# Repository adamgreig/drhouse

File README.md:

DrHouse
=======

House related code. Amongst other things.

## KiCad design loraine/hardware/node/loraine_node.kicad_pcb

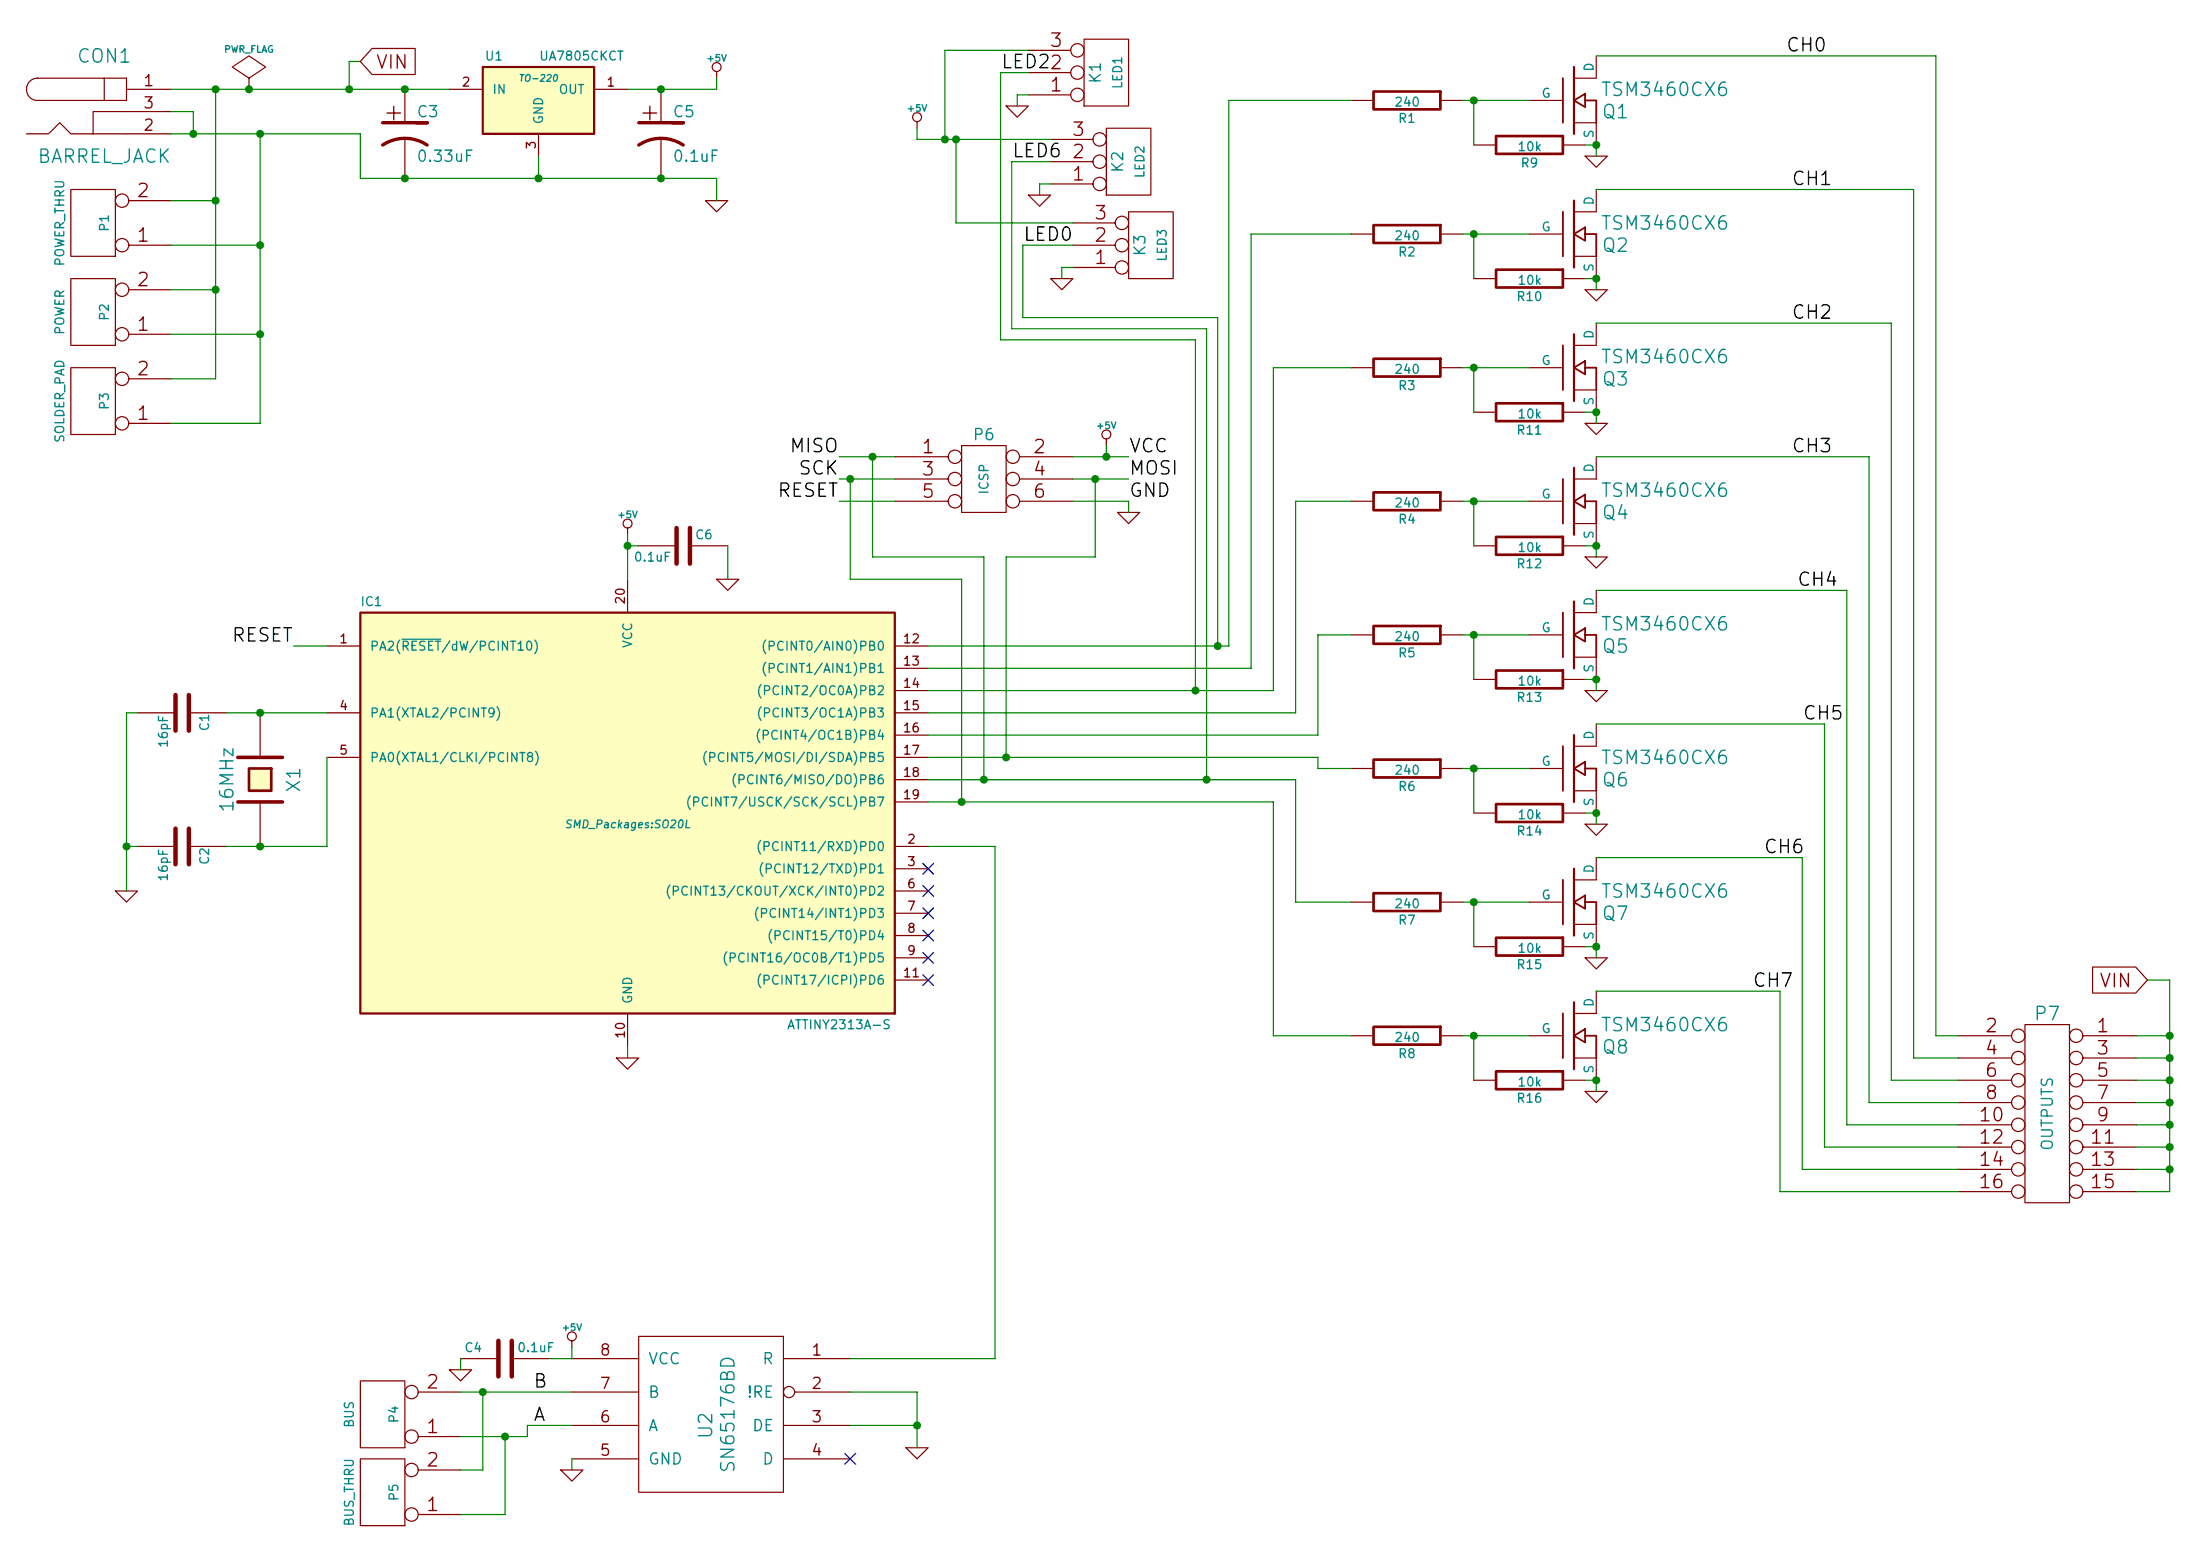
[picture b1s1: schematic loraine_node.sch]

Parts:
C1, C2: 16pF; c_0805
C3: 0.33uF; c_0805
C4, C5, C6: 0.1uF; c_0805
CON1: BARREL_JACK
IC1: ATTINY2313A-S; SO20L
K1: LED1; SIL-3
K2: LED2; SIL-3
K3: LED3; SIL-3
P1: POWER_THRU; SIL-2
P2: POWER; SIL-2
P3: SOLDER_PAD; SIL-2
P4: BUS; Pin_Header_Straight_2x03
P5: BUS_THRU; Pin_Header_Straight_2x08
P6: ICSP; SIL-2
P7: OUTPUTS; SIL-2
Q1, Q2, Q3, Q4, Q5, Q6, Q7, Q8: TSM3460CX6; TO126
R1, R2, R3, R4, R5, R6, R7, R8: 240; SM0805
R9, R10, R11, R12, R13, R14, R15, R16: 10k; SM0805
U1: UA7805CKCT; TO-220
U2: SN65176BD; SO8E
X1: 16MHz; Crystal_HC49-SD_SMD

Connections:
+5V: C4.2, C5.1, C6.2, IC1.20 (VCC), K1.3, K2.3, K3.3, P6.2, U1.1 (OUT), U2.8 (VCC); also elsewhere on the board
/A: P4.1, P5.1, U2.6 (A)
/B: P4.2 (PM), P5.2 (PM), U2.7 (B)
/CH0: P7.2, Q1.D
/CH1: P7.4, Q2.D
/CH2: P7.6, Q3.D
/CH3: P7.8, Q4.D
/CH4: P7.10, Q5.D
/CH5: P7.12, Q6.D
/CH6: P7.14, Q7.D
/CH7: P7.16, Q8.D
/LED0: IC1.12 ((PCINT0/AIN0)PB0), K3.2 (PM), R1.2
/LED2: IC1.14 ((PCINT2/OC0A)PB2), K1.2 (PM), R3.2
/LED6: IC1.18 ((PCINT6/MISO/DO)PB6), K2.2 (PM), P6.1, R7.2
/MOSI: IC1.17 ((PCINT5/MOSI/DI/SDA)PB5), P6.4, R6.2
/RESET: IC1.1 (PA2(~RESET~/dW/PCINT10)), P6.5
/SCK: IC1.19 ((PCINT7/USCK/SCK/SCL)PB7), P6.3, R8.2
GND: C1.2, C2.2, C3.2, C4.1, C5.2, C6.1, CON1.2, CON1.3, IC1.10 (GND), K1.1, K2.1, K3.1, P1.1, P2.1, P3.1, P6.6, Q1.S, Q2.S, Q3.S, Q4.S, Q5.S, Q6.S, Q7.S, Q8.S, R9.1, R10.1, R11.1, R12.1, R13.1, R14.1, R15.1, R16.1, U1.3 (GND), U2.2 (!RE), U2.3 (DE), U2.5 (GND)
unnamed: C1.1, IC1.4 (PA1(XTAL2/PCINT9)), X1.1
unnamed: C2.1, IC1.5 (PA0(XTAL1/CLKI/PCINT8)), X1.2
unnamed 20: IC1.2 ((PCINT11/RXD)PD0), U2.1 (R); also elsewhere on the board
unnamed: IC1.13 ((PCINT1/AIN1)PB1), R2.2
unnamed: IC1.15 ((PCINT3/OC1A)PB3), R4.2
unnamed: IC1.16 ((PCINT4/OC1B)PB4), R5.2
unnamed: Q1.G, R1.1, R9.2
unnamed: Q2.G, R2.1, R10.2
unnamed: Q3.G, R3.1, R11.2
unnamed: Q4.G, R4.1, R12.2
unnamed: Q5.G, R5.1, R13.2
unnamed: Q6.G, R6.1, R14.2
unnamed: Q7.G, R7.1, R15.2
unnamed: Q8.G, R8.1, R16.2
VIN: C3.1, CON1.1, P1.2 (PM), P2.2 (PM), P3.2 (PM), P7.1, P7.3, P7.5, P7.7, P7.9, P7.11, P7.13, P7.15, U1.2 (IN)

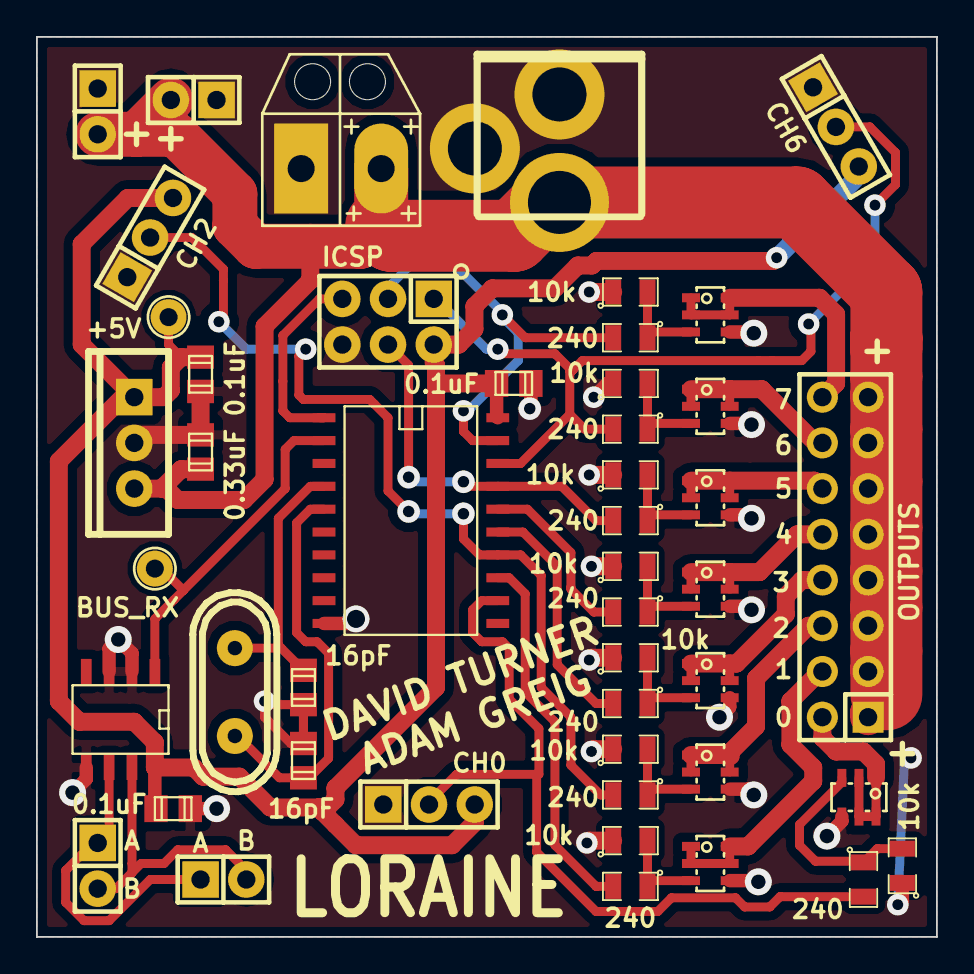
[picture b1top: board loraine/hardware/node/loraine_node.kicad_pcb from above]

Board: 2 copper layers, 50.0 x 50.0 mm, 47 parts (0 on the bottom side), 33 nets.

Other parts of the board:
P8: +5V; TESTPOINT
P9: BUS_RX; TESTPOINT

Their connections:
+5V: P8.1; also elsewhere on the board
unnamed 20: P9.1; also elsewhere on the board

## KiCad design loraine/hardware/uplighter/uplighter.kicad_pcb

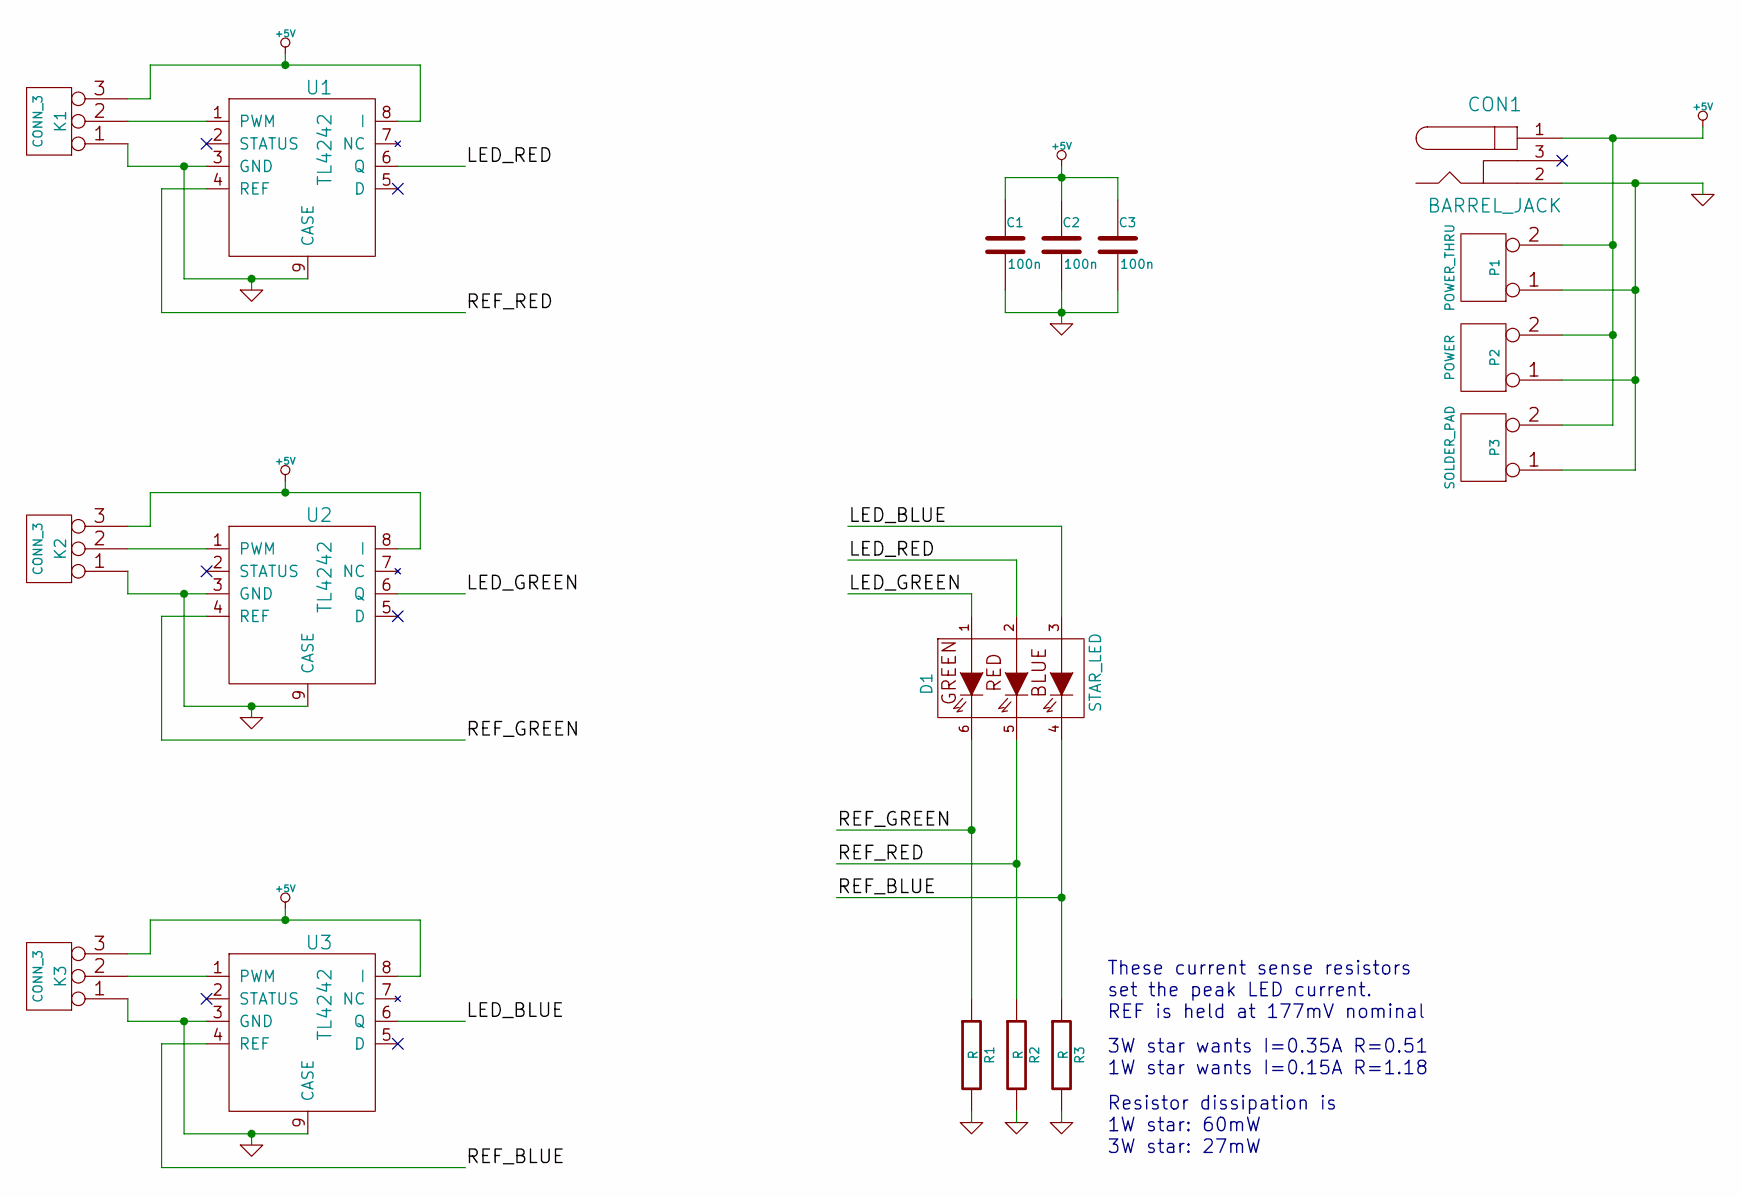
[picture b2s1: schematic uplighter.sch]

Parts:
C1, C2, C3: 100n
CON1: BARREL_JACK
D1: STAR_LED
K1, K2, K3: CONN_3
P1: POWER_THRU
P2: POWER
P3: SOLDER_PAD
R1, R2, R3: R
U1, U2, U3: TL4242

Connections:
+5V: C1.1, C2.1, C3.1, CON1.1, K1.3, K2.3, K3.3, P1.2 (PM), P2.2 (PM), P3.2 (PM), U1.8 (I), U2.8 (I), U3.8 (I)
/LED_BLUE: D1.3 (B+), U3.6 (Q)
/LED_GREEN: D1.1 (G+), U2.6 (Q)
/LED_RED: D1.2 (R+), U1.6 (Q)
/REF_BLUE: D1.4 (B-), R3.1, U3.4 (REF)
/REF_GREEN: D1.6 (G-), R1.1, U2.4 (REF)
/REF_RED: D1.5 (R-), R2.1, U1.4 (REF)
GND: C1.2, C2.2, C3.2, CON1.2, CON1.3, K1.1, K2.1, K3.1, P1.1, P2.1, P3.1, R1.2, R2.2, R3.2, U1.3 (GND), U1.9 (CASE), U2.3 (GND), U2.9 (CASE), U3.3 (GND), U3.9 (CASE)
unnamed: K1.2 (PM), U1.1 (PWM)
unnamed: K2.2 (PM), U2.1 (PWM)
unnamed: K3.2 (PM), U3.1 (PWM)

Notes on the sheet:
These current sense resistors set the peak LED current. REF is held at 177mV nominal
3W star wants I=0.35A R=0.51 1W star wants I=0.15A R=1.18
Resistor dissipation is 1W star: 60mW 3W star: 27mW

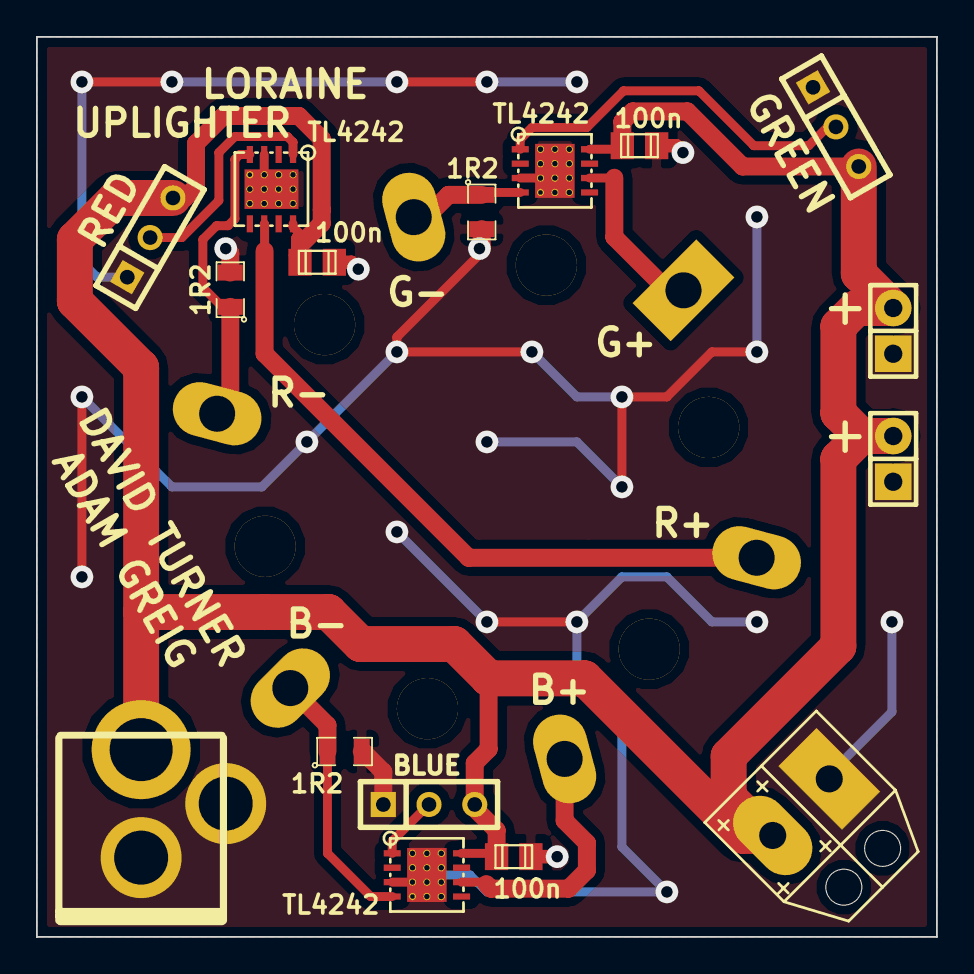
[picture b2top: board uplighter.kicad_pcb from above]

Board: 2 copper layers, 50.0 x 50.0 mm, 17 parts (0 on the bottom side), 11 nets.

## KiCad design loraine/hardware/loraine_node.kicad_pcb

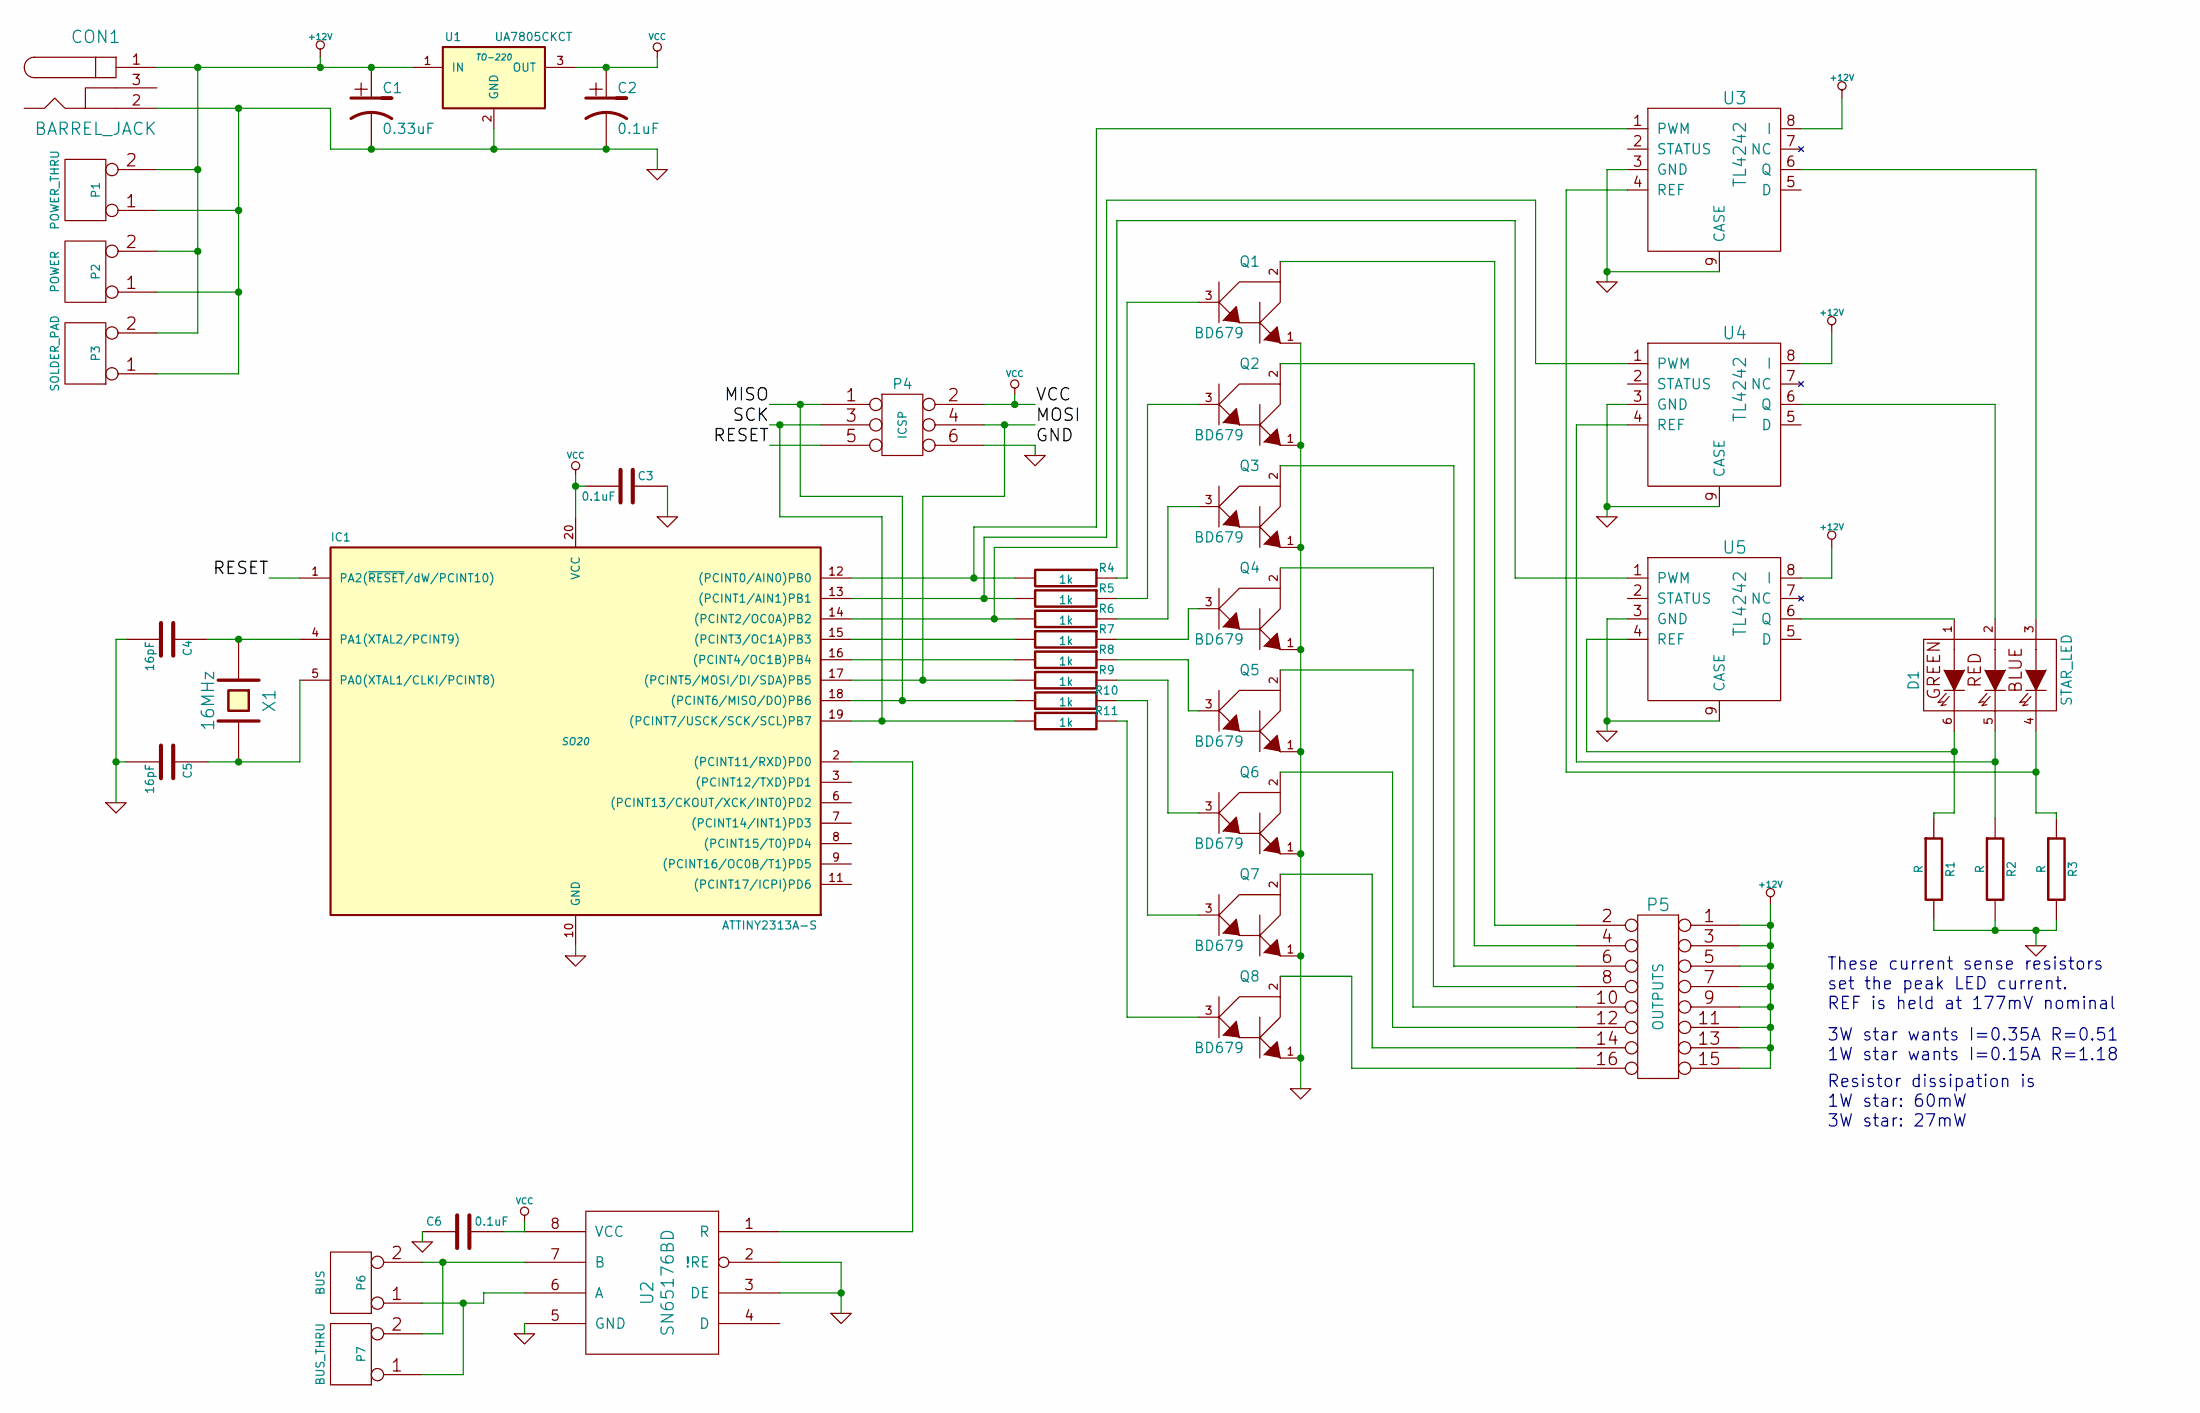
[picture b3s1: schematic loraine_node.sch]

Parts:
C1: 0.33uF
C2, C3, C6: 0.1uF
C4, C5: 16pF
CON1: BARREL_JACK
D1: STAR_LED
IC1: ATTINY2313A-S; SO20
P1: POWER_THRU
P2: POWER
P3: SOLDER_PAD
P4: ICSP
P5: OUTPUTS
P6: BUS
P7: BUS_THRU
Q1, Q2, Q3, Q4, Q5, Q6, Q7, Q8: BD679
R1, R2, R3: R
R4, R5, R6, R7, R8, R9, R10, R11: 1k
U1: UA7805CKCT; TO-220
U2: SN65176BD
U3, U4, U5: TL4242
X1: 16MHz

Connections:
+12V: C1.1, CON1.1, P1.2 (PM), P2.2 (PM), P3.2 (PM), P5.1, P5.3, P5.5, P5.7, P5.9, P5.11, P5.13, P5.15, U1.1 (IN), U3.8 (I), U4.8 (I), U5.8 (I)
/MISO: IC1.18 ((PCINT6/MISO/DO)PB6), P4.1, R10.2
/MOSI: IC1.17 ((PCINT5/MOSI/DI/SDA)PB5), P4.4, R9.2
/RESET: IC1.1 (PA2(~RESET~/dW/PCINT10)), P4.5
/SCK: IC1.19 ((PCINT7/USCK/SCK/SCL)PB7), P4.3, R11.2
GND: C1.2, C2.2, C3.1, C4.2, C5.2, C6.1, CON1.2, IC1.10 (GND), P1.1, P2.1, P3.1, P4.6, Q1.1, Q2.1, Q3.1, Q4.1, Q5.1, Q6.1, Q7.1, Q8.1, R1.2, R2.2, R3.2, U1.2 (GND), U2.2 (!RE), U2.3 (DE), U2.5 (GND), U3.3 (GND), U3.9 (CASE), U4.3 (GND), U4.9 (CASE), U5.3 (GND), U5.9 (CASE)
unnamed: C4.1, IC1.4 (PA1(XTAL2/PCINT9)), X1.1
unnamed: C5.1, IC1.5 (PA0(XTAL1/CLKI/PCINT8)), X1.2
unnamed: D1.1 (G+), U5.6 (Q)
unnamed: D1.2 (R+), U4.6 (Q)
unnamed: D1.3 (B+), U3.6 (Q)
unnamed: D1.4 (B-), R3.1, U3.4 (REF)
unnamed: D1.5 (R-), R2.1, U4.4 (REF)
unnamed: D1.6 (G-), R1.1, U5.4 (REF)
unnamed: IC1.2 ((PCINT11/RXD)PD0), U2.1 (R)
unnamed: IC1.12 ((PCINT0/AIN0)PB0), R4.2, U3.1 (PWM)
unnamed: IC1.13 ((PCINT1/AIN1)PB1), R5.2, U4.1 (PWM)
unnamed: IC1.14 ((PCINT2/OC0A)PB2), R6.2, U5.1 (PWM)
unnamed: IC1.15 ((PCINT3/OC1A)PB3), R7.2
unnamed: IC1.16 ((PCINT4/OC1B)PB4), R8.2
unnamed: P5.2, Q1.2
unnamed: P5.4, Q2.2
unnamed: P5.6, Q3.2
unnamed: P5.8, Q4.2
unnamed: P5.10, Q5.2
unnamed: P5.12, Q6.2
unnamed: P5.14, Q7.2
unnamed: P5.16, Q8.2
unnamed: P6.1, P7.1, U2.6 (A)
unnamed: P6.2 (PM), P7.2 (PM), U2.7 (B)
unnamed: Q1.3, R4.1
unnamed: Q2.3, R5.1
unnamed: Q3.3, R6.1
unnamed: Q4.3, R7.1
unnamed: Q5.3, R8.1
unnamed: Q6.3, R9.1
unnamed: Q7.3, R10.1
unnamed: Q8.3, R11.1
VCC: C2.1, C3.2, C6.2, IC1.20 (VCC), P4.2, U1.3 (OUT), U2.8 (VCC)

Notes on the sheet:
These current sense resistors set the peak LED current. REF is held at 177mV nominal
3W star wants I=0.35A R=0.51 1W star wants I=0.15A R=1.18
Resistor dissipation is 1W star: 60mW 3W star: 27mW

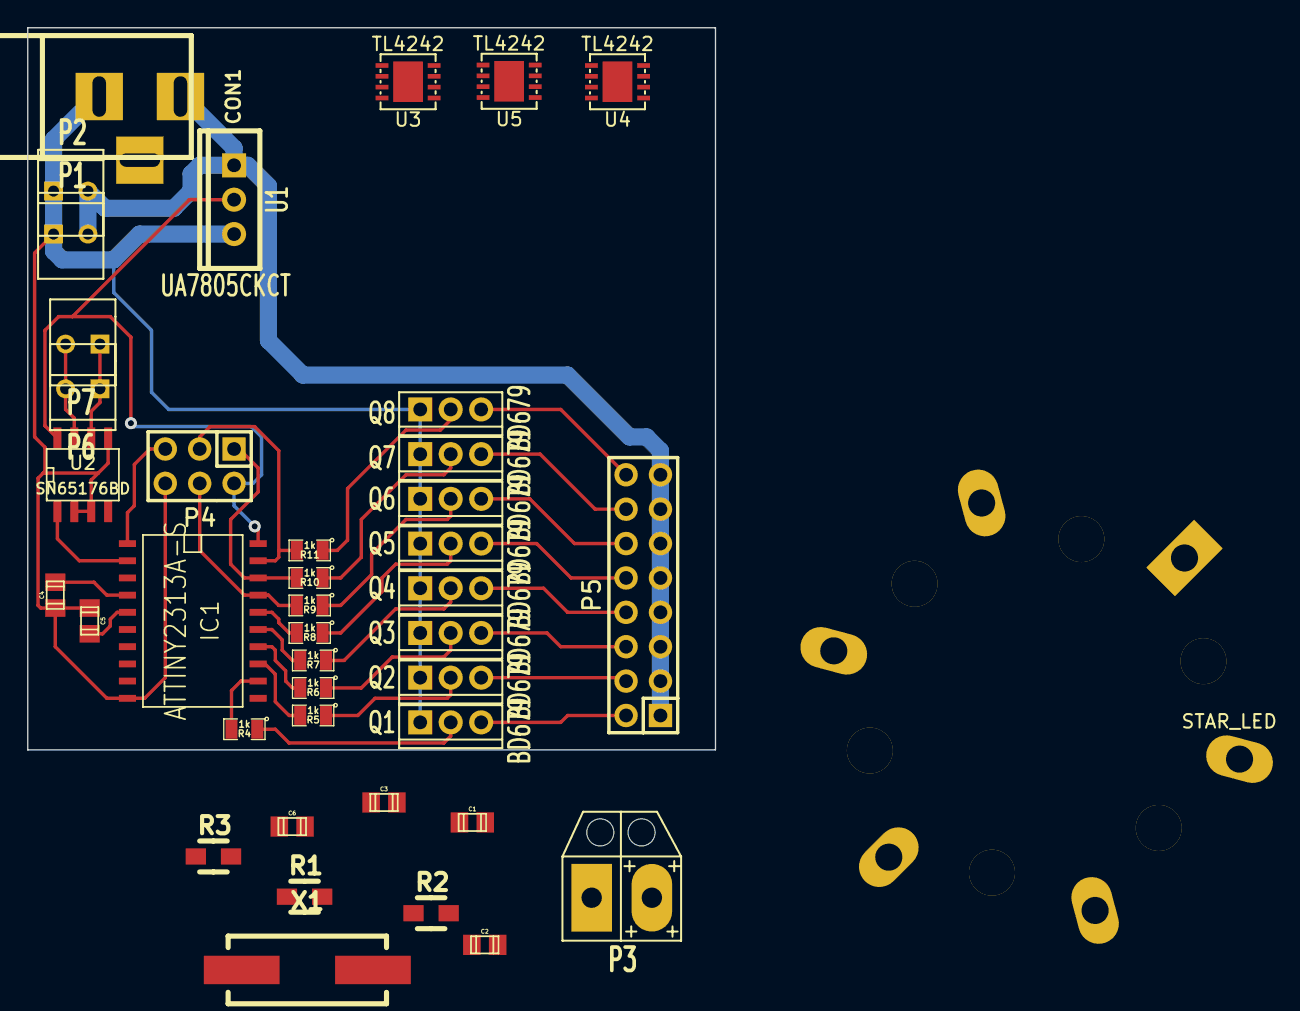
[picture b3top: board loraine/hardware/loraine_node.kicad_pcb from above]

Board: 2 copper layers, 50.8 x 53.3 mm, 41 parts (0 on the bottom side), 39 nets.

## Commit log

2013-12-21 add basic lightstrip control
2013-12-21 fix api bit
2013-12-22 actually use 0-255 on the api
2013-12-22 balance for white point
2013-12-22 colour calibrate against projector
2013-12-23 add android.
2013-12-23 add atmolight
2013-12-23 add beats work
2014-01-25 add first loraine code
2014-01-26 v1 driver and node firmware
2014-01-26 use proper bit names in driver code
2014-01-26 get rid of old prototype driver code
2014-01-27 commit server code
2014-01-28 add broadcast addresses
2014-01-28 add example clients
2014-01-28 Wondering if I can push to this repo.
2014-01-28 Made the vu meter yellow a bit yellower
2014-01-28 Doubled VU speed, made bottom level not always on
2014-01-28 Changed VU speed more for convincing effect
2014-01-28 Initial commit of bookshelf_colour_fade.py
2014-01-28 Slowed frequency of direction changes
2014-01-28 Significant refactor and bugfix
2014-01-28 extend test client to whole bookshelf
2014-01-28 add broadcast test scripts
2014-01-28 Added long shift register to colourfade
2014-01-29 Added stdout flush
2014-01-29 Fixed some code style issues
2014-01-29 Made pep8 happy on bookshelf_colur_fade
2014-01-29 Fixed over-long line in bookshelf_vu
2014-01-29 Doubled frequency of random changes
2014-02-09 Added patternator, example pattern function
2014-02-09 updated comments
2014-02-09 Added random_hue patternator
2014-02-09 Add random_hue_walk patternator
2014-02-09 Fixed style err in example_pattern
2014-02-10 temp to rgb transform
2014-02-10 Simplified incandescent simulator
2014-02-10 Changed colours slightly in test_inc
2014-02-11 inctest2 with hand tuned incandescent fade vals
2014-02-11 add cserver
2014-02-11 fit functions based on hand tuned inc sim
2014-02-11 unsigned chars for server.c
2014-02-11 add first go at loraine python lib
2014-02-11 Removed debug message from libloraine
2014-02-11 Updated loraine clients to cserver
2014-02-12 Changed inctest2 to interpolation method
2014-02-12 add comment to driver sketch
2014-02-12 Changed test_incandescent to interp method
2014-02-12 Added basic patternator wrapper
2014-02-12 add first go at VU
2014-02-19 Disabled debug output in bookshelf_colour_fade
2014-02-20 Added patternator incandescent flash
2014-02-24 TODO with fun randombow plans
2014-03-03 Added new incandescent_set script
2014-03-30 Uplighter node hardware schematic
2014-03-30 KiCAD .gitignore file
2014-03-30 Added extra power connectors
2014-03-30 Added ICSP header
2014-03-30 Added common anodes to outputs connector
2014-03-30 Filled in most component values
2014-03-30 Replaced VCC/GND labels with symbols
2014-03-31 Specced darlington drivers
2014-03-31 fairylights!
2014-03-31 py2 compat
2014-03-31 add auto lights
2014-03-31 Initial netlist and most parts
2014-03-31 basic pcb component spread
2014-03-31 Added kicad_pcb-bak to .gitignore
2014-03-31 First attempt at PCB, minus some caps and LEDs
2014-03-31 Changed darlingtons to PTH part
2014-03-31 Added bus thu connector
2014-03-31 PCB rev2
    Routed PTH darlingtons
    swapped order of output pinout to make pcb route better
    'L'-shaped PCB for adam ;)
2014-03-31 Added TL4242 driver ICs with support circuitry
2014-03-31 Moved driver PWM conns to before BJT base resistors.
2014-04-30 Fixed driver current sense lines
    TL4242 current sense lines went to ground instead of top of current sense resistors.
2014-04-30 Added star_led schematic component
    Made new library star_led.lib with schematic component for RGB star LED with pinout matching Farnell 1716741. Footprint to follow.
2014-05-01 Annotated schematic, annotated netlist
2014-05-01 Added TL4242 footprint
2014-05-01 Added star led module footprint
2014-05-01 Added outline to 8-SON footprint
2014-05-01 Added remaining footprints to netlist/pcb
2014-05-01 Added locking 2-way MOLEX headers
    MOLEX part 22-23-2021 for header = farnell 1462926
    MOLEX part 22-01-3027 for receptacle = farnell 1462825
2014-05-01 Added proper solder pad footprint
2014-05-01 Improved power solder pad
    Added strain relief, made pin 1 (negative) rectangular
2014-05-04 Updated BOM
2014-05-09 renamed dir
2014-05-09 Changed LED component/footprint to single colour devices
2014-05-10 Split project into node and uplighter
    Node now contains ATTINY, bus controller and most logic and programing
    Uplighter board is just three LEDs and their drivers (and sense resistors)
    Connection between the two is currently a SIL9 but might be better split into three (or so) connectors so the connectors can stably mount the uplighter board.
2014-05-10 Split board-board connector to 3x SIL3
2014-05-11 Removed separate uplighter board
2014-05-12 Proposed design: 1 board 3x3 RGB LEDs
2014-05-12 Fixed sense resistors in schematic
2014-05-18 Heatsunk LED footprint and board pads
2014-05-18 Square board edge
2014-05-18 Split boards
    Removed LEDs and TL4242s and sense resistors from main node board and added 3x SIL3 connectors
    Added 2nd board containing heatsunk LED mounting, TL4242, sense resistors.
2014-05-19 Added backside copper and thermal vias to 8-son
2014-07-17 Proposed output driver for node h/w
2014-07-20 NMOS drivers on schematic + ERC fixes
2014-07-20 Node PCB redo
2014-07-20 Finished footprint placement on node board
2014-07-20 Cleared up node pcb silk
2014-07-20 Finished both PCBs apart from logos and checking
2014-07-21 5V power conn on uplighter board
2014-07-22 Added solder_pad to uplighter pcb dir
2014-07-22 Minor changes b/c of TODOs
2014-07-22 Some more mods based on checking stuff in TODO
2014-07-23 Re-layed-out and rerouted uplighter pcb
2014-07-27 Derouted, chunkified PTH pads
2014-07-27 Ninja-edit to make routing nicer
2014-07-27 Rerouted loraine node board -- much nicer!
2014-07-27 Prettified PCB
2014-07-27 Adam's changes and gerbils
2014-07-27 Added revision and date to silk
2014-07-27 Proper gerber extensions
2014-07-28 Added TPs to node
2014-07-28 Nominally finished both PCBs
2014-07-28 Soldermask under LGAs to make rework easier
2014-07-28 Modified barrel jacks to keep silk inside board edge
2014-07-28 Renaming drill file format extensions
2014-08-01 Node and uplighter part sel. and costing
2014-08-16 PCB paste files
2014-08-19 Updated node BOM for order
2014-08-21 simple node test firmware
2014-12-17 Made astral module only required for automode
